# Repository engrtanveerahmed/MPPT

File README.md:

# Maximum Power Point Tracking (MPPT)

## Introduction
We know that sun light is varriable during day some time is low some time it's intensity is high specially at mid of day its intensity is high due to this our solar pannel gives varriable voltages we intensity is high our normal solar pannel 12 voltes rated  gives 14or 15 voltages and if it is connected to 12v rated bettery this extra voltages is really hazerd for our bettry in ordr to remove this hazerd we design Maximun power point trackin solar charge controller (MPPT).

## Design requirements
In todays world design in project play inportant it requires to main key parameters one is we can carry it any where easily number two it is eye catching, in order to do we made design on autocade and also we are blessed with fablab that contain 3D printer with help of that we made our 3D design

## Project excuting plan
We have distribute our task in to two member so that beacause in short time we have alot of work to do bellow chart contain our flow of doing work. 

## Destributinsion of tasks

## Higher level Diagram

## Description of Principle of Operations
MPPT Min work is to gives stable (12)voltageg at out put this work (step down) is done by the buck converter, at in put and out we used voltage and current sensior; voltages divder circuit at input and output Which sensed voltages developed on the input and gives it to an analogue pin of microcontroller. also a current sense amplifier is attached using a shunt resistor on the main input section. There is also a voltage divider circuit on the output section where the battery is connected. A current sense amplifier is used on the output section as well. These all values are fed to the microcontroller. Depending upon these values, microcontroller decides about the PWM signal fed to the Half-Bridge Mosfet Driver IC. this IC takes input as a PWM signal and switches the MOSFETs with a very high speed. The Buck converter acts according to the decission made by microcontroller depending upon the input and output currents and voltages.

## Bill of material

## Desciption of Major Components of project
##### Microcontroller:

The low-power Microchip 8-bit AVR RISC-based microcontroller featuring 32KB self-programming flash program memory, 2.5KB SRAM, 1KB EEPROM, USB 2.0 full-speed/low speed device, 12-channel 10-bit A/D-converter, and JTAG interface for on-chip-debug. The device achieves up to 16 MIPS throughput at 16 MHz. 2.7 - 5.5 Volt operation. We have used this microcontroller because of its lower consemption and usb support. its features helped us to replace arduino with this microcintroller in project.

###### USB mini:
The small USB is used in digitil devices like digital cameras, external hard drives, USB hubs and other equipment. Mini USB is much smaller than USB Type A and B but twice as thick as Micro USB. We have used this componant as we could burn our code easily on the microcontroller.

##### INA213 (Current sense amplifier):
The INA21x are voltage-output, current-shunt monitors (also called current-sense amplifiers) that are commonly used for overcurrent protection, precision-current measurement for system optimization, or in closed-loop feedback circuits. This series of devices can sense drops across shunts at common-mode voltages from 0.3 V to 26 V, independent of the supply voltage. Six fixed gains are available: 50 V/V, 75 V/V, 100 V/V, 200 V/V, 500 V/V, or 1000 V/V. The low offset of the zero-drift architecture enables current sensing with maximum drops across the shunt as low as 10-mV full-scale. These devices operate from a single 2.7-V to 26-V power supply, drawing a maximum of 100 uA of supply current. All versions are specified over the extended operating temperature range (40°C to +125°C), and offered in SC70 and UQFN packages. We have used this componant as to sense the input and output voltage/current to track the working of the MPPT.

##### IR2104 (Half-bridge):
The discrete Half-bridge driver based on IR2104 gate driver IC and low impedance high current N channel IRFP4368 MOSFETS , The IR2104 is a high voltage, high speed power MOSFET driver with independent high and low side referenced output channels. We have used this componant to derive the mosfets.

##### Schottky Diode :
The Schottky Diode is a type of semiconductor diode which have the advantage that their forward voltage drop is substantially less than that of the conventional silicon pn-junction diode. Schottky diodes have many useful applications from rectification, signal conditioning and switching, through to TTL and CMOS logic gates due mainly to their low power and fast switching speeds.

)

##### IPB136n08n3 (PWR-MOSFET):
These are ideal for high frequency switching. Optimized technology for DC/DC converters. Excellent gate charge x R product N-channel, normal level. 100% avalanche tested. Pb-free plating; RoHs compliant.

)

Shunt Resistors:
Shunt resistors are used with current sense amplifier to sense the current.

##### Voltage Regulator LM7805:
We are using this voltage regulator because the input voltage is 12 voltages and our microcintroller and some other componants run on 5V so its is regulating the voltages. It is easily available for use.

##### Zener Diode::
We are using zener diode if our input voltage increases from the circuit limitations, it will directly ground the voltages.

###### Connectivity to components (Protocol)
As we have used Atmega32U4 microcontroller, which has the support to connect a USB, so we are using Universal serial bus for the connectivity of our board with PC to burn the code into it.
## Electrical Schematic
The schematic diagram is taken from the Eagle file we have developed for our final PCB:

## Brief Description of Schematic
Here we define our project more clearily.

##### Microcontroller and its required components:
The microcontroller is the key component of this whole circuit as it is making decissions on the basis of values it is receiving. the components attached with microcontroller in "1" are chosen according to the Arduino Leonardo which uses the same Microcontroller. An ICSP header is also connected to burn the boadloader on to the microcontroller. The connection of a USB MINI are also made with the microcontroller.

##### Input Voltage Divider Circuit:
This circuit divides the input voltage to such a level in which microcontroller can sense it because if we attach the microcontroller directly, it cannot bear the voltage and will burnout intantly. So we have to reduce the voltage to such a level which can be given to microcontroller. We used a 39kiloohm resistor and a 10 kilo ohm resistor to make the ratio appropriate. Also two zener voltages are connected in parallel for we want input voltage not more than a certain value.
##### Input Current Sense Amplifier:
INA213, a current sense amplifier is connected here to sense the input current. The shunt resistor helps this IC to sense the current and then this IC gives output to the Microcontroller which then displays it on the LCD.

##### Half Bridge Driver IC and Buck Converter:
The IR2104, a half bridge MOSFET driver takes input of PWM signal from the microcontroller and then performs the switching of the MOSFETs. Hence controlling the output current and voltage.

##### Output Current Sense Amplifier:
It works on the same principle as the input current sense amplifier.

##### Output Voltage Regulator:
Volatge regulator is developed here for the same reason, the only difference is the voltage for division. Here the voltage is 12V. So, we connected a 22 kilo-ohm resistor in series with a 10 kilo-ohm resistor.

##### LCD connectors:
these connectors are attached for the display which will be mounted on the casing.

##### Power Headers and Voltage Regulator:
The three headers for 12 volts Supply(on which the board will operate), Panel(to take input from solar panel) and Output(for the output voltage taken from the circuitry ). The voltage regulator is connected because we are using 12V supply on which the IC IR2104 operates but all other ICs need 5V to operate so we are using this LM7805 for this purpose.

## PCB Layout

We used Eagle software to develop the PCB for our project and we created the layouts in .PNG formats as the Milling Machine available in Fablab needs picture format for its processing. Following is the final PCB layout:

## Challenges While Routing
Whille routing the PCB it consumed a lot of out time because the circuit we were following used a separate board for microcontroller but our aim was to embed both the circuit on a single layer, making it more compact. This came with lots of hurdles while routing, we used few zero ohm resitor to overcome routing issues and at the end developed a lot more compact circuit after tens of attempts.

## Bill of Material on taped on a Paper
Following is the Picture of the components taken from the FabLab

## Picture of Clean Printed Circuit Board
For fabrication of our PCB, we used SRM-20(Rolland's mills) machine. It needs a monochrome picture for its processing. the monochrome picture we took from Eagle software were then uploaded to the "Fab-Modules.org" and then we generated the ".rml" files needed for SRM-20 to process the milling.

.jpeg?raw=true)

## Picture of Populated Circuited Board
After fully soldering teh components, our board looked like this:

.jpeg?raw=true)

## Procedure adopted to burn Bootloader
To burn the boot loader on to the microcontroller, we used ICSP header and arduino IDE. we burnt the bootloader of Arduino leonardo onto the ATmega32U4. For this we followed the following steps:
1. connetcing th board with PC through ICSP header and a USB mini cable for further burning the test code.
2. selecting the board through "Tools" menu.
3. in tools, further going to submenu "Select Board".
4. selecting "Arduino Leonardo".
5. again going to "tools" menu and then selecting the submenu "Port" and then select the port on which ICSP is connected.
6. again going to another submenu "Programmer" and selecting "AVRISP mkll" .
7. last step is to select the last most option of "burn the bootloader".
8. wait for few minutes till it shows the message on status bar as "Done burning Bootloader.".

## Picture of successfully operating circuit

## Picture of fully assembled System

.jpeg)

## The FlowChart of our software design

## Main Functions of the code
##### buck_setup() Function::
This function is designed to set up the timer to generate PWM signal. It initializes the timer with the desired duty cycle to set the circuit up.
##### buck_enable() Function:
This method is written so to enable the clock source and then turns on the Half bridge driver through PWM signal.
##### buck_disable() Function:
TThis functtion turns off the clock source and sets the duty cycle of PWM signal to zero.
##### buck_duty(unit8_t duty) Function:
This function checks the duty cycle of the and stes it to the appropriate value for the operation of the Buck converter. it Arranges the duty cycle to an optimum level.
##### write_display() Function:
This function is utlized to write on the LCD. it tfakes values from several values and displays them along with some text on the LCD.
##### read_values() Function:
This function takes the values from the volatge divider circuits and current sense amplifiers and sets them correctly after callibration.
##### buck_update() Function:
This method is the key function in the code which calls some of the above functions and updates the duty cucle accordingly.

## Challenges faced while coding
The major problem we faced during the coding for this project was configuring the timer for generatng PWM signal. We tried to configure different available timers using different PWM pins on the board. First we configured timer1 using PWM pin 9, but this timer was a 16 bit timer which brought a lot of problems because our major calculations were based on the 8 bit timer. so after struggling a lot we obtained a maximum volatge of 7.44V at the output. Furthermore we connected our Half bridge driver with PWM pin 11 and using timer0 we obtained the exact output.

## CAD Design of Enclosure
For Casing of our prodcut, we used both laser Cut and 3D-printing. We wanted to consume lesser filament for 3D-printing thats why we thought of making the top of the casing clear to make it a bit unique. So, we made the top using laser cut. We designed a locking mechanism of Slide and press. We slide one side of the top and press the other towards the bottom.

## CAD Design with Dimensions
Followings are the CAD design pictures with dimensions:

## Business model

Every product which needs to be in the market requires a good business plan. for our product, we considered few major point regarding its cost and its users. As our project is user friendly in terms of its size, the size increases the durability. One can carry it anywhere to be used. Furthermore, solar charges(MPPT based) are very expensive products, we used such components which are commonly available and are cheap. With these two major advantages, we hope to cover a good number of users of our products when released in the market.

## References

[soldernerd web site link review](https://soldernerd.com/2016/01/21/arduino-mppt-solar-charger-shield/)

[Basics of MPPT Solar Charge Controller](http://www.leonics.com/support/article2_14j/articles2_14j_en.php)

[AVR-ATmega16U4-32U4_Datasheet](http://ww1.microchip.com/downloads/en/DeviceDoc/Atmel-7766-8-bit-AVR-ATmega16U4-32U4_Datasheet.pdf)

[Leonardo Timer trouble…](https://forum.arduino.cc/index.php?topic=125252.)

[Tanveer Ahmed (Stutentof Sukkur IBA University, Pakistan)](https://github.com/engrtanveerahmed)

[MPPT Autocade Design file](https://github.com/engrtanveerahmed/MPPT/tree/main/Autocade%20design%20file)

[Mppt Eagle file](https://github.com/engrtanveerahmed/MPPT/tree/main/Eagle%20file)

[Mppt Audino Source Code file](https://github.com/engrtanveerahmed/MPPT/tree/main/source%20code/SolarPanelchk)

## Conclusion
This project was full of learning.We made PCB cricuit three time, the reanson in first board our USB mini port beacme short while sodering because the have small pins we learnt that do soldering carifully a single mistake can distured whole PCB, we made a seconde PCB this time we do soldering care fully but our circuit became short beacuse circuit is large so for this we check continuity test but it work was really time consuming because circuit is large finally we made last circuit it works our pervious PCB boards don not go weste we leart alot from them,but this not good practice because material goes weste we need do things carefully while making eagle file Dia of SRM matchune when it comes to microcontroller, soldering selection of component like we add big capactor which consume whole size of our PCB, We had a lot of practical interaction with our theoratical knowledge. This project proved a golden oppurtunity as we implemented most of our theoratical knowledge.Milling a PCB, designing an enclosure.etc. all of these experiences proved fruitful in increasing our skills and capabilty to do experiments and troubleshooting. In future, we have decided to continue such kind of practice for further learning and skill development.

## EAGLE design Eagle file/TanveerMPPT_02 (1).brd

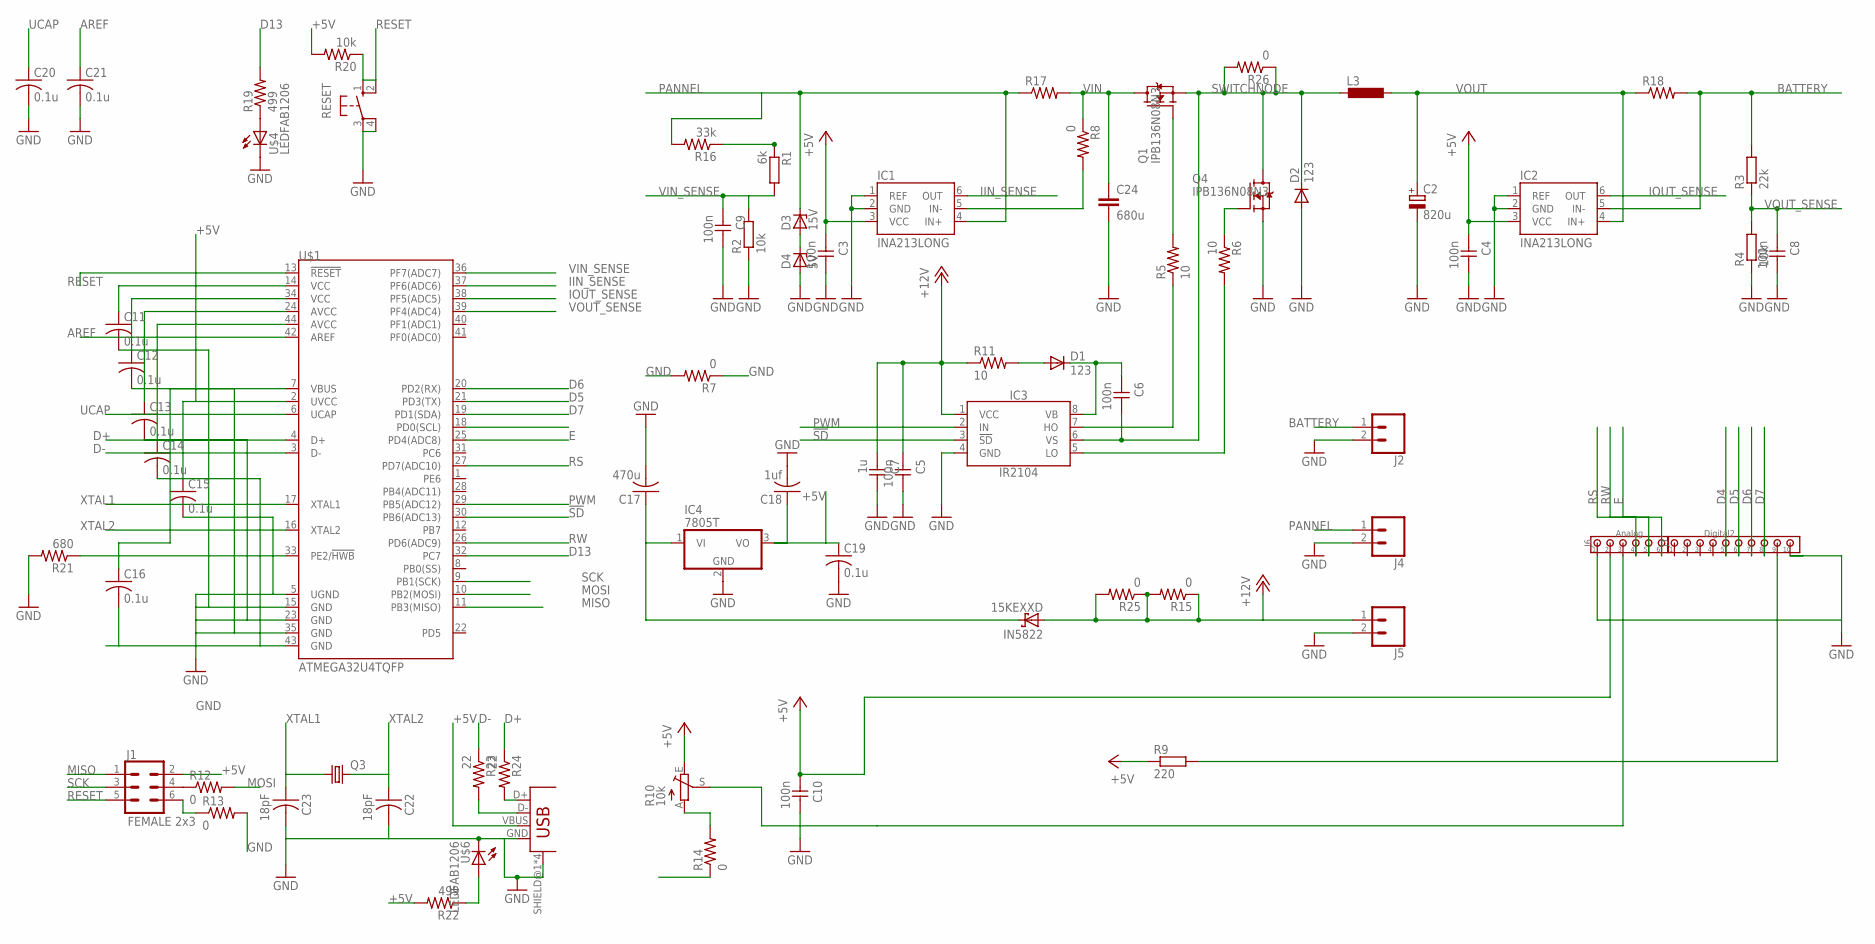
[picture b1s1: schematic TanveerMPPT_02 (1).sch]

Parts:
C2: 820u; 10MM
C3, C8: 100n; C1206
C4, C5, C6, C9, C10: 100n; C1206FAB
C7: 1u; C1206FAB
C11, C12, C13, C14, C15, C16, C19, C20, C21: 0.1u; C1206
C17: 470u; C1206
C18: 1uf; C1206
C22, C23: 18pF; C1206FAB
C24: 680u; CAP-PTH-10MM
D1, D2: 123; DO41-10
D3: 15V; DO41Z10
D4: 5V; DO41Z10
IC1, IC2: INA213LONG; SC70-6_LONG
IC3: IR2104; SOIC8
IC4: 7805T; TO220H
IN5822: 15KEXXD; DO201T15
J1: FEMALE 2x3; 2X3
J2, J4, J5: CONN_02PTH4; 1X02_XTRA_BIG
J3: Digital2; 100MIL_10X_ROUND
J6: Analog; 100MIL_6X_ROUND
L3: L-EUIR-4; IR-4
Q1, Q4: IPB136N08N3; TO263-3
Q3: CRYSTALTC26V; TC26V
R1: 6k; M1206
R2, R4: 10k; M1206
R3: 22k; M1206
R5, R6, R11: 10; R1206FAB
R7, R8, R12, R13, R14, R15, R25, R26: 0; R1206FAB
R9: 220; M1206
R10: 10k; B25X
R16: 33k; R1206FAB
R17, R18: R-US_R2512; R2512
R19: 499; R1206FAB
R20: 10k; R1206
R21: 680; R1206FAB
R22: 499; R1206
R23, R24: 22; R1206
RESET: 10-XX; B3F-10XX
U$1: ATMEGA32U4TQFP; SPARKFUN-DIGITALIC_TQFP44
U$4, U$6: LEDFAB1206; LED1206FAB
U$5: USB_MINIB

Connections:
!SD!: IC3.3 (!SD!), U$1.30 (PB6(ADC13))
+5V: C3.1, C4.1, C10.1, C11.1, C12.1, C13.1, C14.1, C15.1, C16.1, C18.1, C19.1, IC1.3 (VCC), IC2.3 (VCC), IC4.3 (VO), J1.2, J6.2, R9.1, R10.E, R20.2, R22.2, U$1.2 (UVCC), U$1.7 (VBUS), U$1.14 (VCC), U$1.24 (AVCC), U$1.34 (VCC), U$1.44 (AVCC), U$5.VBUS
+12V: C5.1, C7.1, IC3.1 (VCC), IN5822.A, J5.1, R11.1, R15.1, R15.2, R25.1, R25.2
AREF: C21.1, U$1.42 (AREF)
BATTERY: IC2.5 (IN-), J2.1, R3.2, R18.2
D4: J3.5, U$1.18 (PD0(SCL))
D5: J3.6, U$1.21 (PD3(TX))
D6: J3.7, U$1.20 (PD2(RX))
D7: J3.8, U$1.19 (PD1(SDA))
D13: R19.2, U$1.32 (PC7)
D+: R24.1, U$1.4 (D+)
D-: R23.1, U$1.3 (D-)
E: J6.6, U$1.25 (PD4(ADC8))
GND: C2.-, C3.2, C4.2, C5.2, C7.2, C8.2, C9.2, C10.2, C11.2, C12.2, C13.2, C14.2, C15.2, C16.2, C17.2, C18.2, C19.2, C20.2, C21.2, C22.2, C23.2, C24.2, D2.A, D4.A, IC1.1 (REF), IC1.2 (GND), IC2.1 (REF), IC2.2 (GND), IC3.4 (GND), IC4.2 (GND), J2.2, J3.10, J4.2, J5.2, J6.1, Q4.3 (S), R2.1, R4.1, R7.1, R7.2, R10.A, R13.2, R14.1, R14.2, R21.2, RESET.3, RESET.4 (P1), U$1.5 (UGND), U$1.15 (GND), U$1.23 (GND), U$1.35 (GND), U$1.43 (GND), U$4.2 (C), U$5.GND, U$5.SHIELD@1 (SHIELD), U$5.SHIELD@2 (SHIELD), U$5.SHIELD@3 (SHIELD), U$5.SHIELD@4 (SHIELD), U$6.2 (C)
IIN_SENSE: IC1.6 (OUT), U$1.37 (PF6(ADC6))
IOUT_SENSE: IC2.6 (OUT), U$1.38 (PF5(ADC5))
MISO: J1.1, U$1.11 (PB3(MISO))
MOSI: R12.2, U$1.10 (PB2(MOSI))
unnamed: J1.4, R12.1
unnamed: J1.6, R13.1
unnamed: IC1.5 (IN-), R8.2
unnamed: Q1.1 (G), R5.2
unnamed: Q4.1 (G), R6.1
unnamed: J3.9, R9.2
unnamed: J6.3, R10.S
unnamed: D1.A, R11.2
unnamed: C6.1, D1.C, IC3.8 (VB)
unnamed: IC3.7 (HO), R5.1
unnamed: IC3.5 (LO), R6.2
unnamed: R1.1, R16.1
unnamed: D3.A, D4.C
unnamed: C17.1, IC4.1 (VI), IN5822.C
unnamed: R19.1, U$4.1 (A)
unnamed: R21.1, U$1.33 (PE2/!HWB)
unnamed: R24.2, U$5.D+
unnamed: R22.1, U$6.1 (A)
unnamed: R23.2, U$5.D-
PANNEL: D3.C, IC1.4 (IN+), J4.1, R16.2, R17.1
PWM: IC3.2 (IN), U$1.29 (PB5(ADC12))
RESET: J1.5, R20.1, RESET.1 (S), RESET.2 (S1), U$1.13 (!RESET)
RS: J6.4, U$1.27 (PD7(ADC10))
RW: J6.5, U$1.26 (PD6(ADC9))
SCK: J1.3, U$1.9 (PB1(SCK))
SWITCHNODE: C6.2, D2.C, IC3.6 (VS), L3.2, Q1.3 (S), Q4.TAB (D), R26.1, R26.2
UCAP: C20.1, U$1.6 (UCAP)
VIN: C24.1, Q1.TAB (D), R8.1, R17.2
VIN_SENSE: C9.1, R1.2, R2.2, U$1.36 (PF7(ADC7))
VOUT: C2.+, IC2.4 (IN+), L3.1, R18.1
VOUT_SENSE: C8.1, R3.1, R4.2, U$1.39 (PF4(ADC4))
XTAL1: C23.1, Q3.1, U$1.17 (XTAL1)
XTAL2: C22.1, Q3.2, U$1.16 (XTAL2)

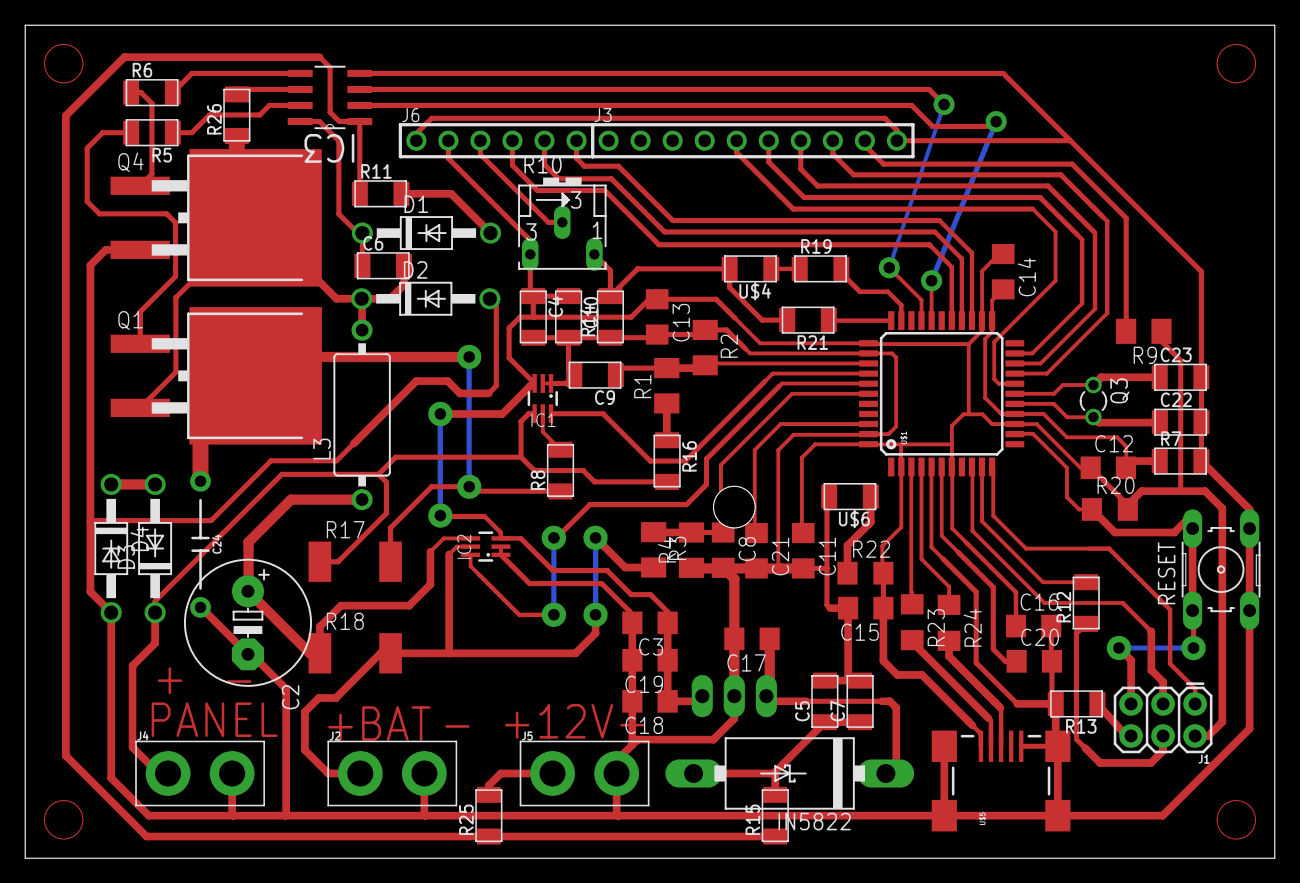
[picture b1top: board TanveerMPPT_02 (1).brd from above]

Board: 2 copper layers, 99.1 x 66.0 mm, 73 parts (1 on the bottom side), 51 nets.

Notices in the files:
parts and their libraries:
SparkFun-Retired: Licensing: Creative Commons ShareAlike 4.0 International - https://creativecommons.org/licenses/by-sa/4.0
